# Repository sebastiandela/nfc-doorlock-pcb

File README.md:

# NFC-Controlled Electromagnetic Door Lock (Custom PCB)

The design files for a custom PCB created in Fusion 360 for an **NFC-controlled electromagnetic door lock**.

A **12V power supply** is used to power the eletromagnetic lock, NFC reader, and ATmega328P core. The schematic uses the Arduino Nano as the base and adds the additional functionality. 

## PCB Installation
This is an example of how the PCB can be used in a system.

## Board Layout

## 3D Model

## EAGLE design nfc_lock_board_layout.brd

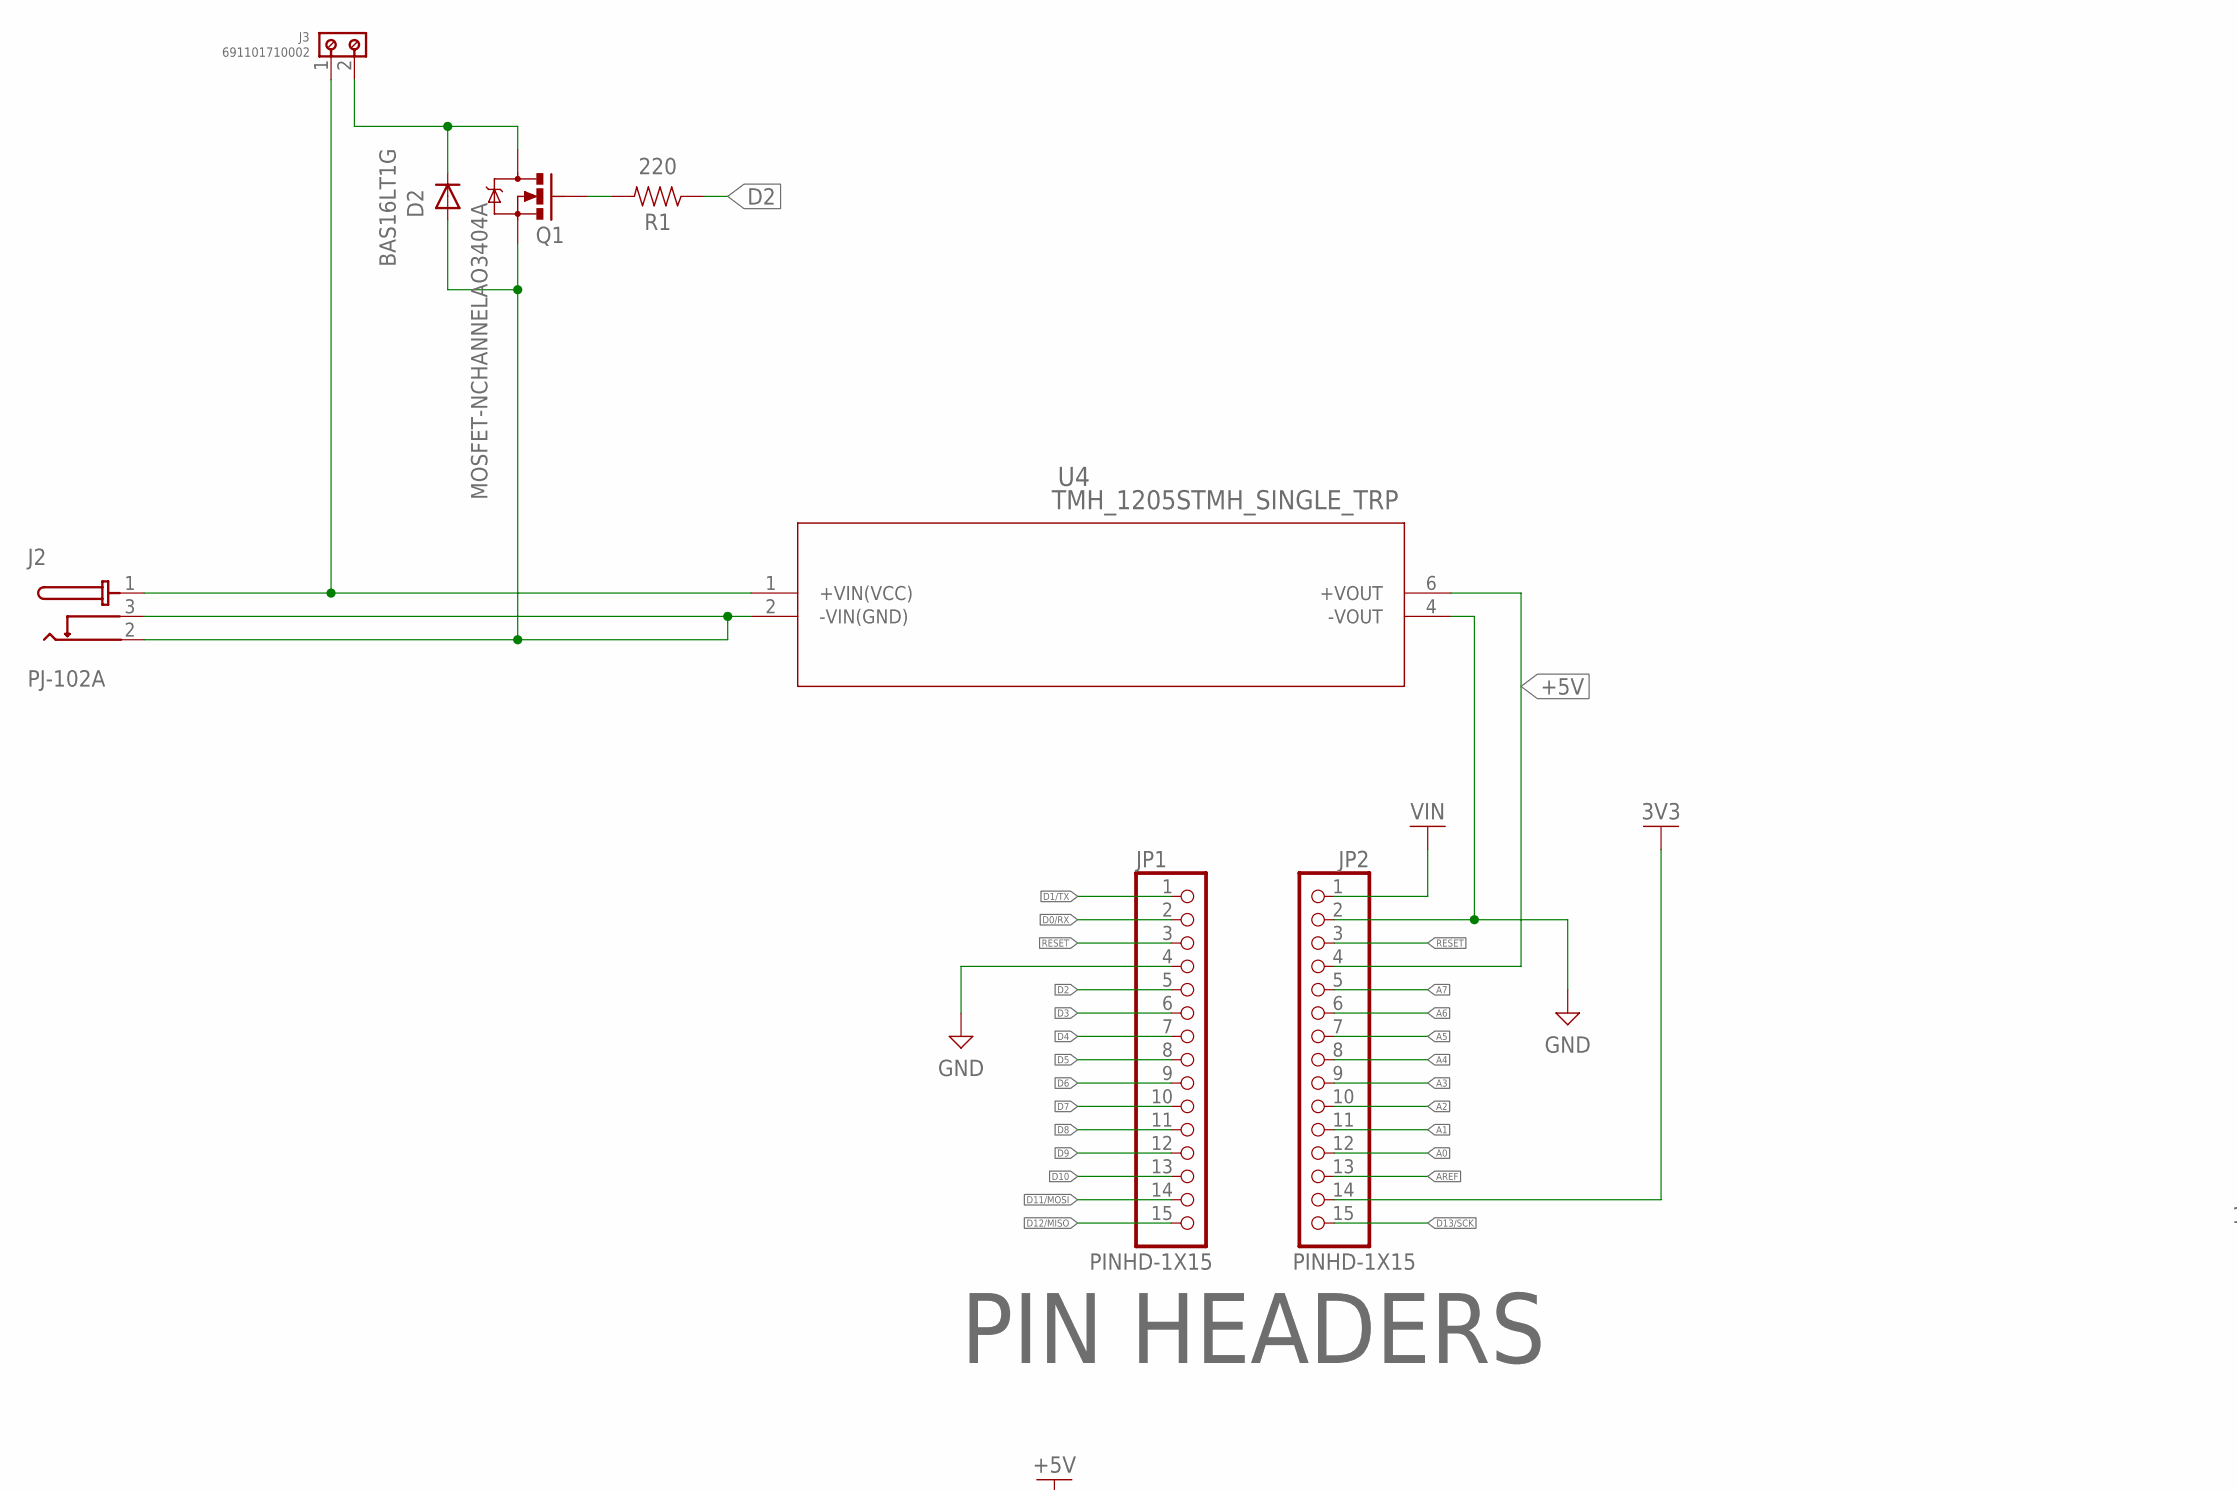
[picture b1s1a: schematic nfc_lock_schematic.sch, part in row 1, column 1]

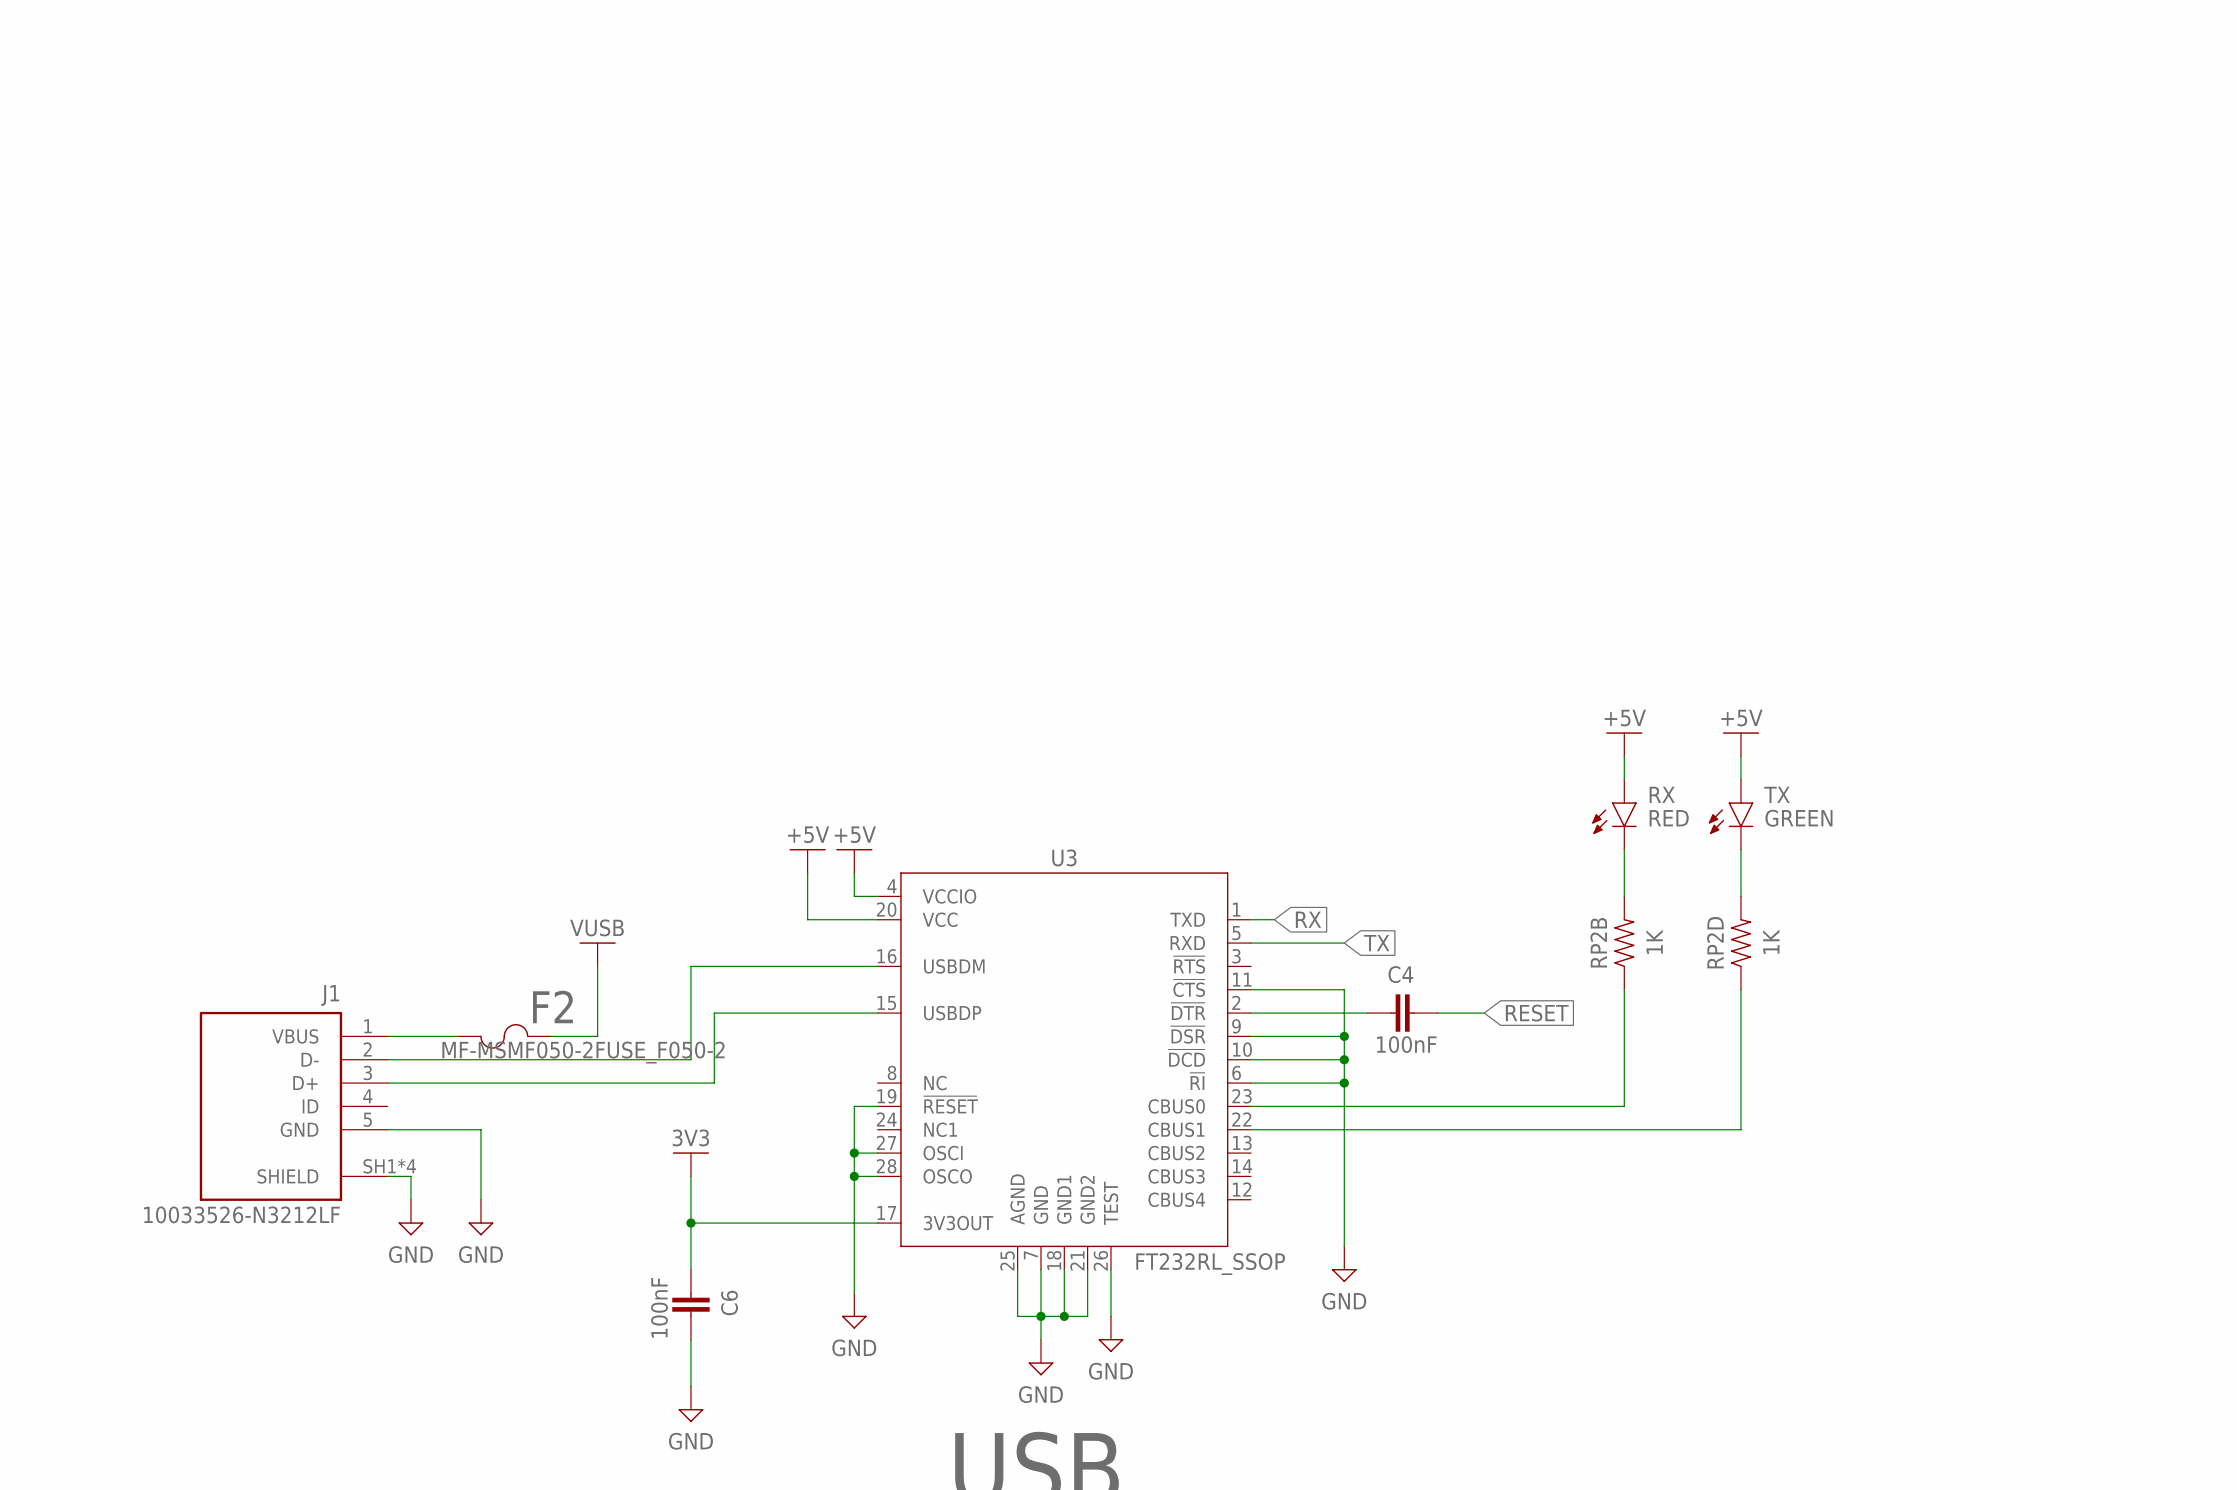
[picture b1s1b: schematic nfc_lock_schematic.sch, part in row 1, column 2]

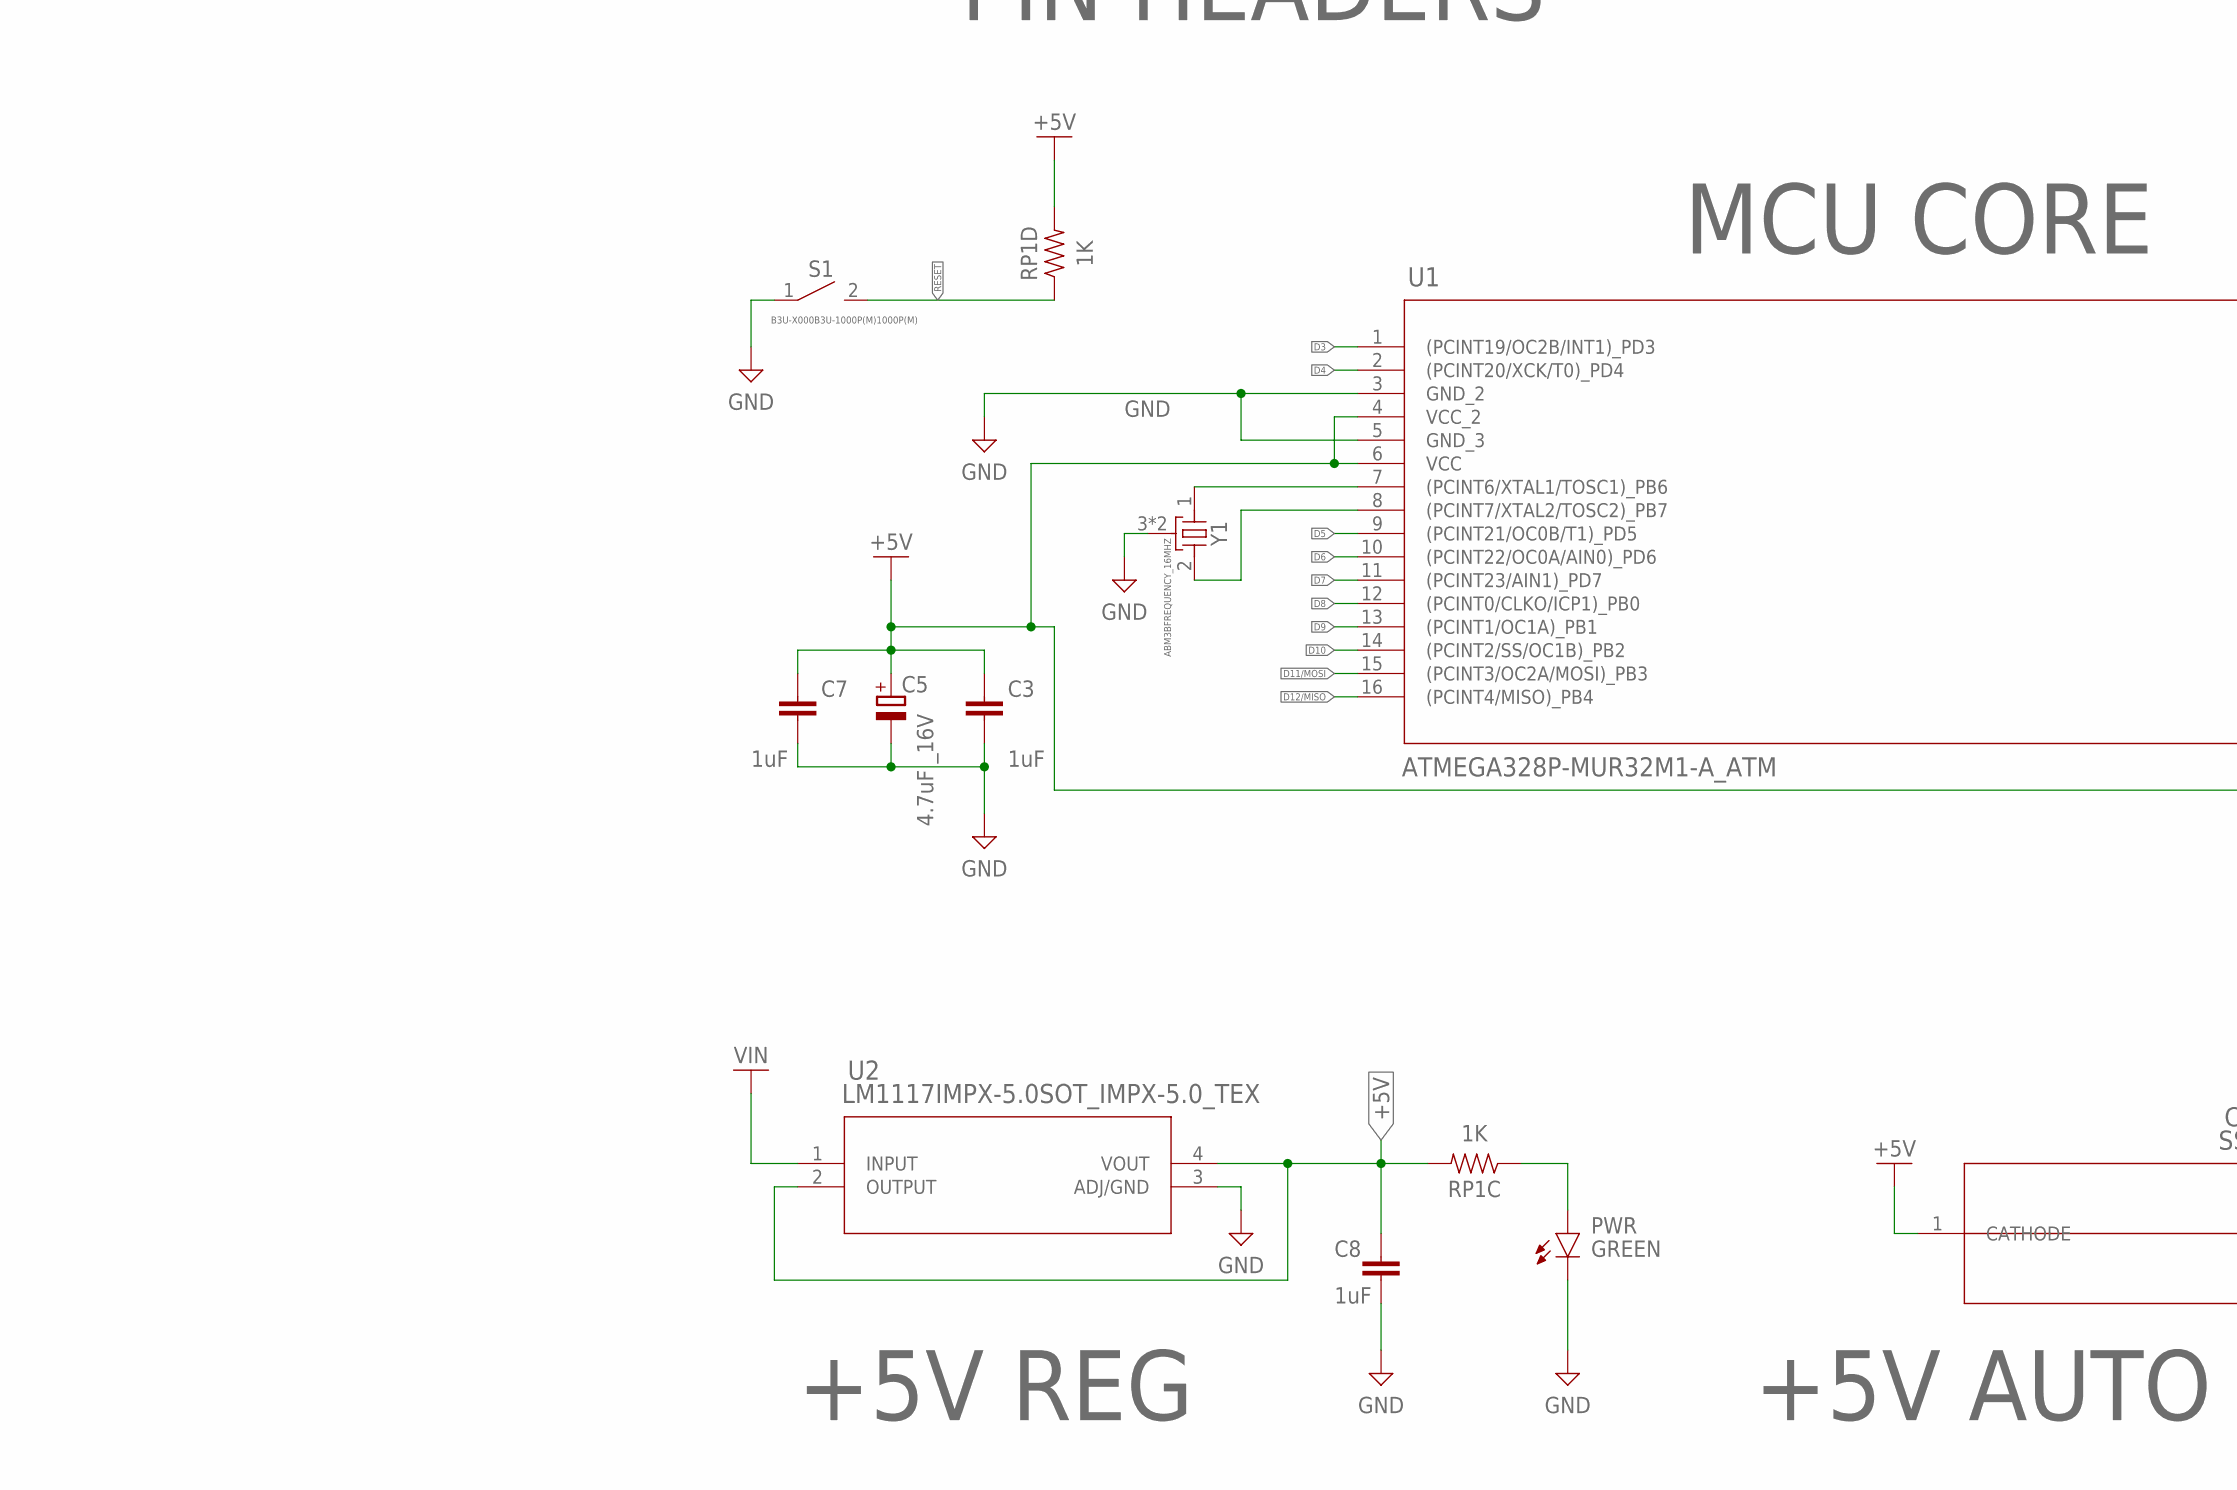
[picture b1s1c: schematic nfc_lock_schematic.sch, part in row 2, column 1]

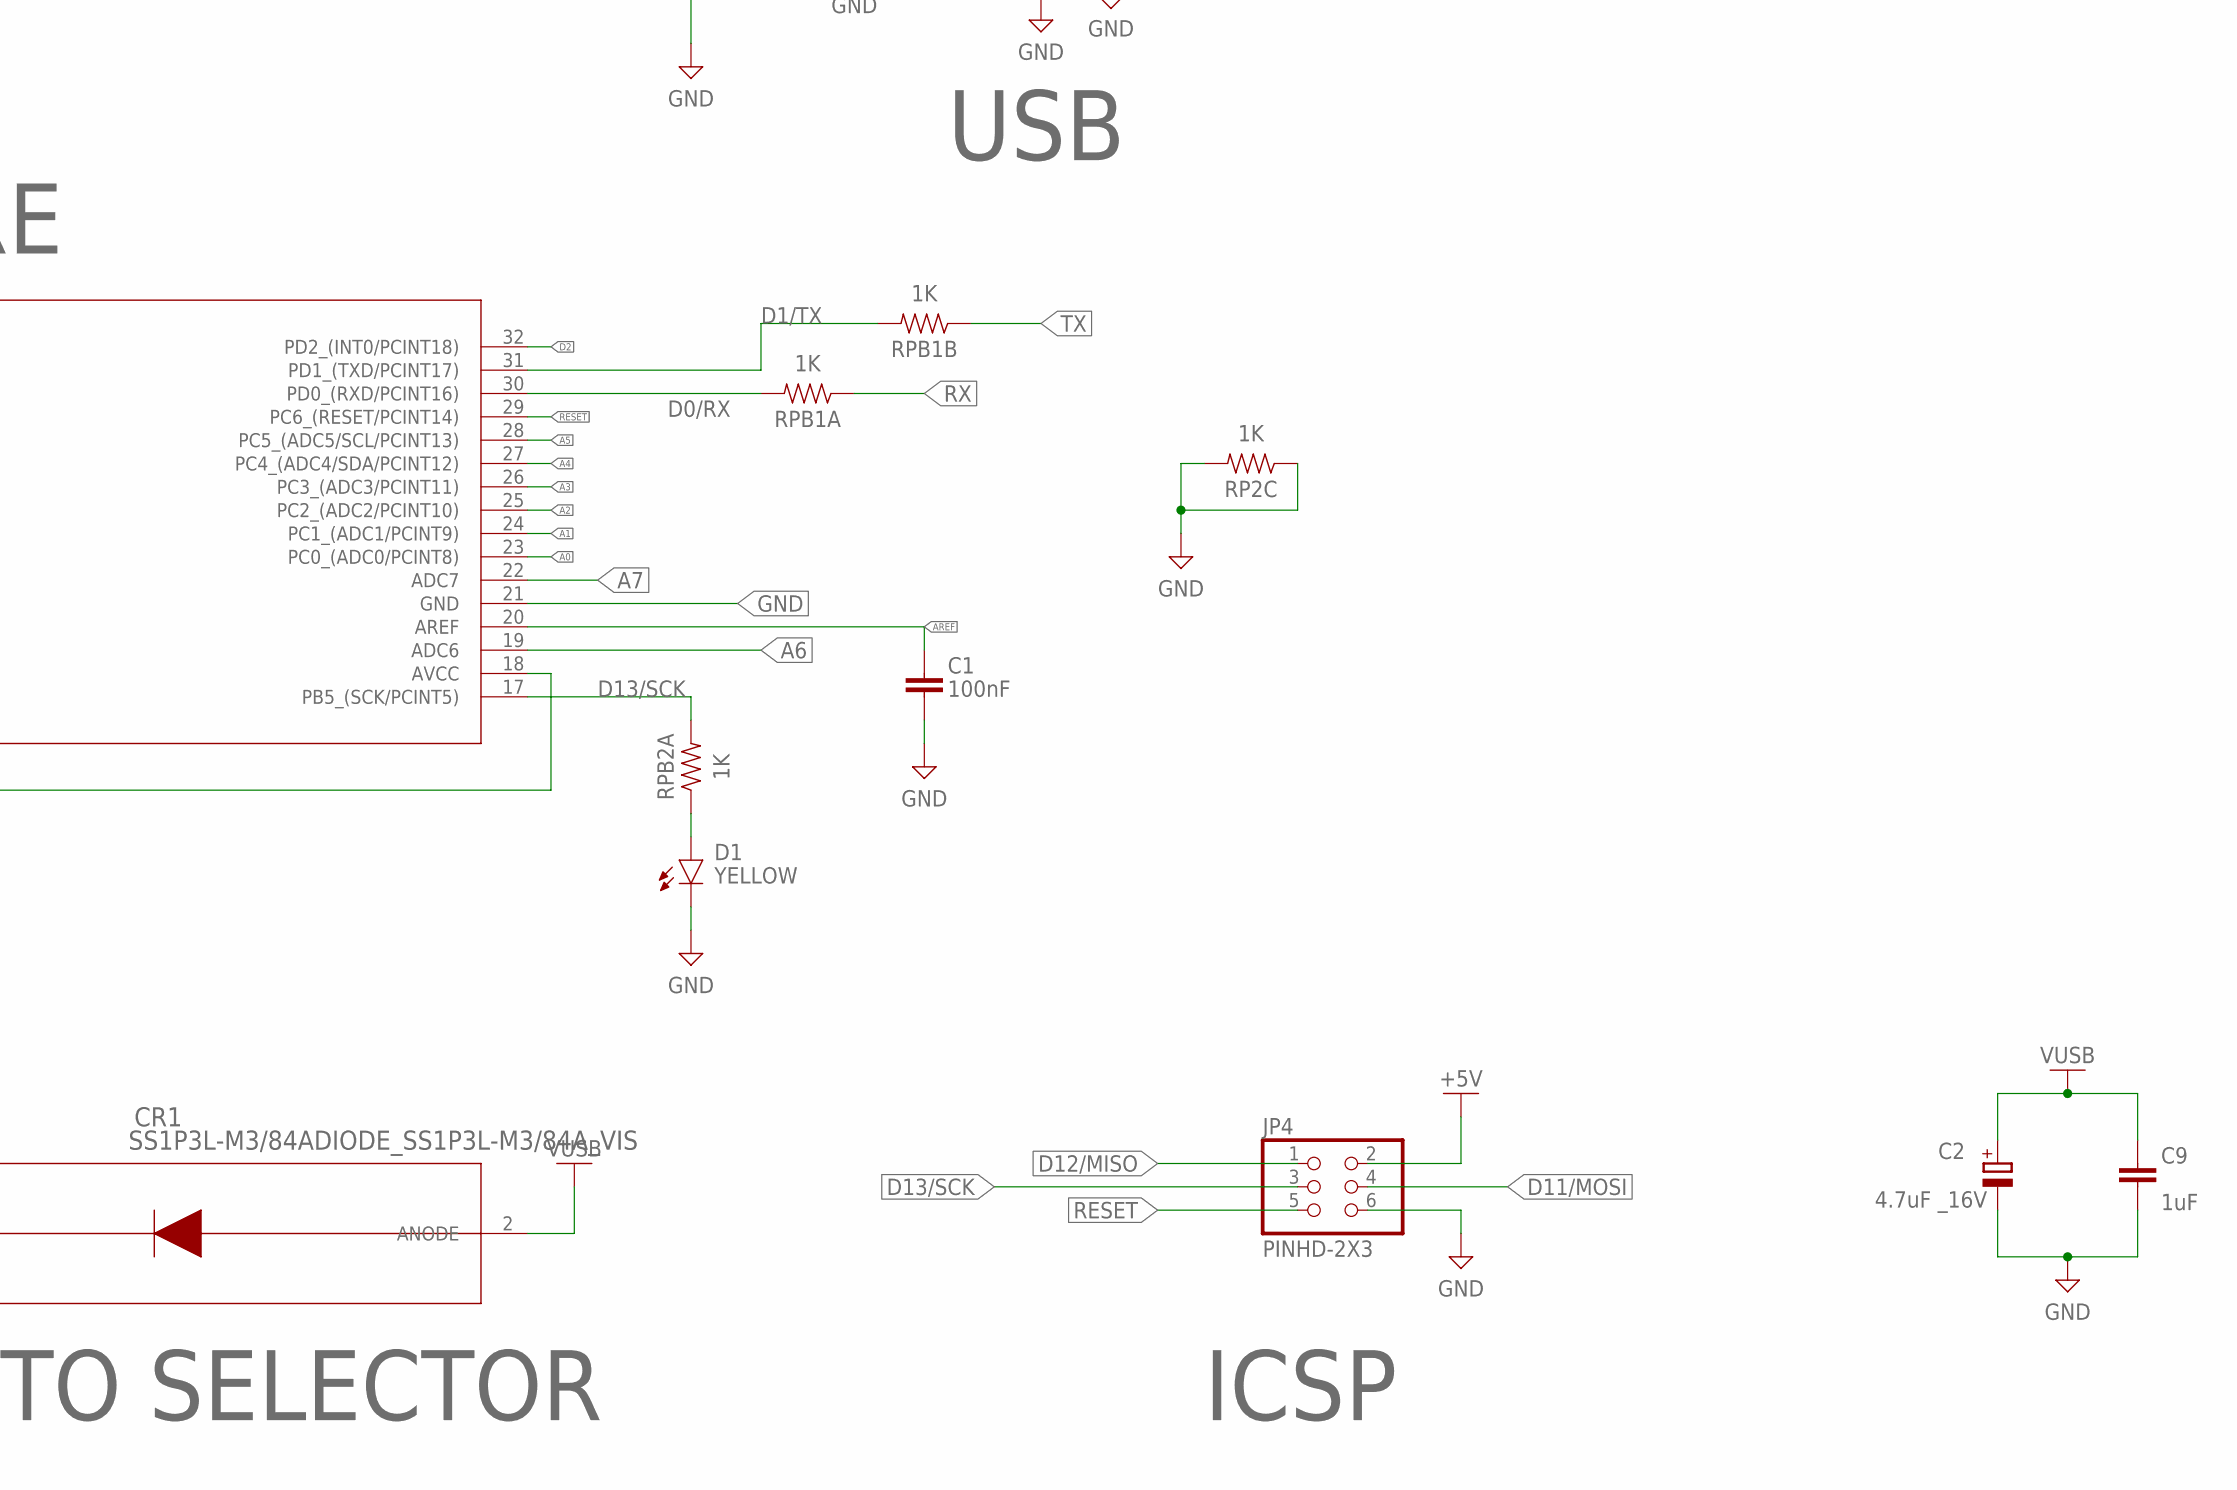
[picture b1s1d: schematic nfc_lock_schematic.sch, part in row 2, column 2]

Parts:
C1, C4, C6: 100nF; CAPC1005X60
C2, C5: 4.7uF _16V; CAPMP3216X180N
C3, C7, C8, C9: 1uF; CAPC1005X60
CR1: SS1P3L-M3/84ADIODE_SS1P3L-M3/84A_VIS; DIODE_SS1P3L-M3/84A_VIS
D1: YELLOW; LEDC1608X35N_FLAT-Y
D2: BAS16LT1G; SOT23
F2: MF-MSMF050-2FUSE_F050-2; FUSE_F050-2
J1: 10033526-N3212LF; AMPHENOL_10033526-N3212LF
J2: PJ-102A; CUI_PJ-102A
J3: 691101710002
JP1, JP2: PINHD-1X15; 1X15
JP4: PINHD-2X3; 2X03
PWR: GREEN; LEDC1608X35N_FLAT-G
Q1: MOSFET-NCHANNELAO3404A; SOT23-3
R1: 220; RESC1005X40
RP1C, RP1D, RP2B, RP2C, RP2D: 1K; RESC1005X40
RPB1A, RPB1B, RPB2A: 1K; RESC1005X40
RX: RED; LEDC1608X35N_FLAT-R
S1: B3U-X000B3U-1000P(M)1000P(M); B3U-1000P(M)
TX: GREEN; LEDC1608X35N_FLAT-G
U1: ATMEGA328P-MUR32M1-A_ATM; 32M1-A_ATM
U2: LM1117IMPX-5.0SOT_IMPX-5.0_TEX; SOT_IMPX-5.0_TEX
U3: FT232RL_SSOP; SSOP28
U4: TMH_1205STMH_SINGLE_TRP; TMH_SINGLE_TRP
Y1: ABM3BFREQUENCY_16MHZ; OSCSC500X320X110-4N

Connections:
3V3: C6.1, JP2.14, U3.17 (3V3OUT)
+5V: C3.1, C5.1 (+), C7.1, C8.1, CR1.1 (CATHODE), JP2.4, JP4.2, RP1C.2, RP1D.2, RX.A, TX.A, U1.4 (VCC_2), U1.6 (VCC), U1.18 (AVCC), U2.2 (OUTPUT), U2.4 (VOUT), U3.4 (VCCIO), U3.20 (VCC), U4.6 (+VOUT)
A0: JP2.12, U1.23 (PC0_(ADC0/PCINT8))
A1: JP2.11, U1.24 (PC1_(ADC1/PCINT9))
A2: JP2.10, U1.25 (PC2_(ADC2/PCINT10))
A3: JP2.9, U1.26 (PC3_(ADC3/PCINT11))
A4: JP2.8, U1.27 (PC4_(ADC4/SDA/PCINT12))
A5: JP2.7, U1.28 (PC5_(ADC5/SCL/PCINT13))
A6: JP2.6, U1.19 (ADC6)
A7: JP2.5, U1.22 (ADC7)
AREF: C1.1, JP2.13, U1.20 (AREF)
D0/RX: JP1.2, RPB1A.2, U1.30 (PD0_(RXD/PCINT16))
D1/TX: JP1.1, RPB1B.2, U1.31 (PD1_(TXD/PCINT17))
D2: JP1.5, Q1.1 (G), R1.1, R1.2, U1.32 (PD2_(INT0/PCINT18))
D3: JP1.6, U1.1 ((PCINT19/OC2B/INT1)_PD3)
D4: JP1.7, U1.2 ((PCINT20/XCK/T0)_PD4)
D5: JP1.8, U1.9 ((PCINT21/OC0B/T1)_PD5)
D6: JP1.9, U1.10 ((PCINT22/OC0A/AIN0)_PD6)
D7: JP1.10, U1.11 ((PCINT23/AIN1)_PD7)
D8: JP1.11, U1.12 ((PCINT0/CLKO/ICP1)_PB0)
D9: JP1.12, U1.13 ((PCINT1/OC1A)_PB1)
D10: JP1.13, U1.14 ((PCINT2/SS/OC1B)_PB2)
D11/MOSI: JP1.14, JP4.4, U1.15 ((PCINT3/OC2A/MOSI)_PB3)
D12/MISO: JP1.15, JP4.1, U1.16 ((PCINT4/MISO)_PB4)
D13/SCK: JP2.15, JP4.3, RPB2A.2, U1.17 (PB5_(SCK/PCINT5))
GND: C1.2, C2.2 (-), C3.2, C5.2 (-), C6.2, C7.2, C8.2, C9.2, D1.C, J1.5 (GND), J1.SH1 (SHIELD), J1.SH2 (SHIELD), J1.SH3 (SHIELD), J1.SH4 (SHIELD), JP1.4, JP2.2, JP4.6, PWR.C, RP2C.1, RP2C.2, S1.1, U1.3 (GND_2), U1.5 (GND_3), U1.21 (GND), U2.3 (ADJ/GND), U3.6 (!RI), U3.7 (GND), U3.9 (!DSR), U3.10 (!DCD), U3.11 (!CTS), U3.18 (GND1), U3.19 (!RESET), U3.21 (GND2), U3.25 (AGND), U3.26 (TEST), U3.27 (OSCI), U3.28 (OSCO), U4.4 (-VOUT), Y1.3 (GND), Y1.4 (GND)
unnamed: U1.8 ((PCINT7/XTAL2/TOSC2)_PB7), Y1.2
unnamed: U1.7 ((PCINT6/XTAL1/TOSC1)_PB6), Y1.1
unnamed: PWR.A, RP1C.1
unnamed: D1.A, RPB2A.1
unnamed: C4.1, U3.2 (!DTR)
unnamed: RP2B.1, U3.23 (CBUS0)
unnamed: RP2B.2, RX.C
unnamed: RP2D.1, U3.22 (CBUS1)
unnamed: RP2D.2, TX.C
unnamed: F2.2, J1.1 (VBUS)
unnamed: J1.2 (D-), U3.16 (USBDM)
unnamed: J1.3 (D+), U3.15 (USBDP)
unnamed: J2.1, J3.1, U4.1 (+VIN(VCC))
unnamed: D2.3 (K), J3.2, Q1.3 (D)
unnamed: D2.1 (A), J2.2, J2.3, Q1.2 (S), U4.2 (-VIN(GND))
RESET: C4.2, JP1.3, JP2.3, JP4.5, RP1D.1, S1.2, U1.29 (PC6_(RESET/PCINT14))
RX: RPB1A.1, U3.1 (TXD)
TX: RPB1B.1, U3.5 (RXD)
VIN: JP2.1, U2.1 (INPUT)
VUSB: C2.1 (+), C9.1, CR1.2 (ANODE), F2.1

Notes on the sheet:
MCU CORE
+5V REG
+5V AUTO SELECTOR
ICSP
PIN HEADERS
USB

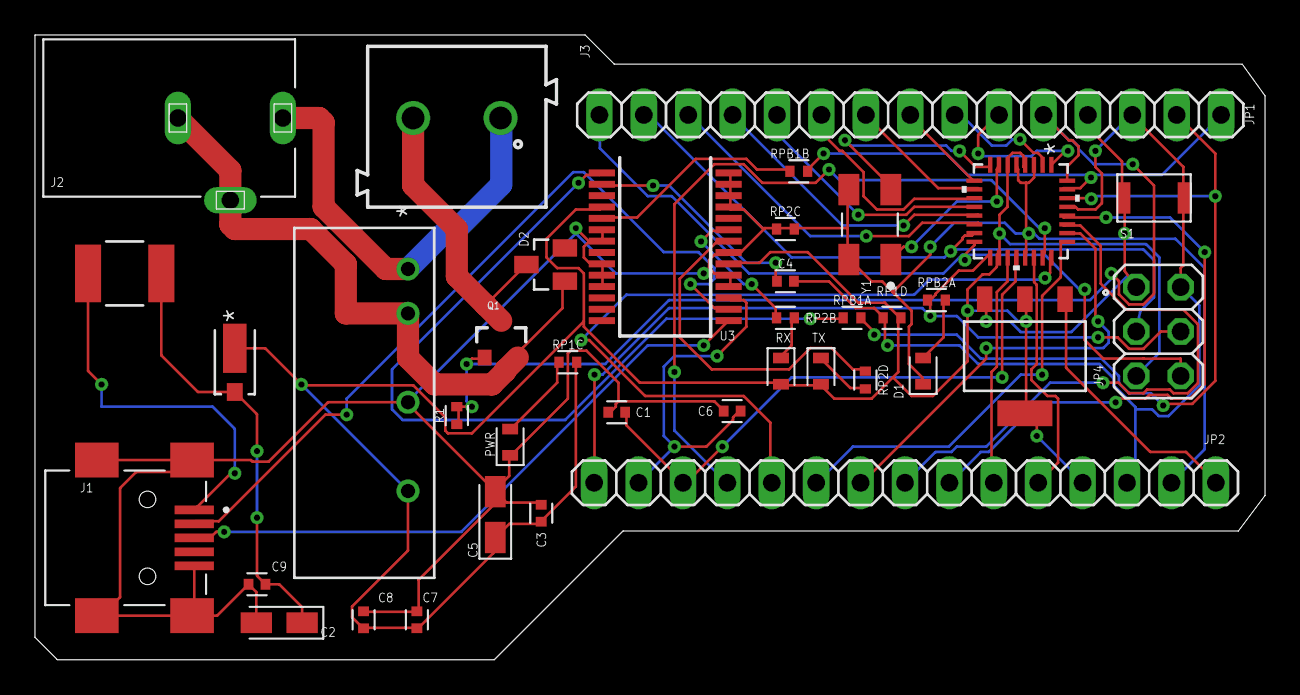
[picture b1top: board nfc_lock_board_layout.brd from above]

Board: 2 copper layers, 70.4 x 35.7 mm, 38 parts (0 on the bottom side), 46 nets.

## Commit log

2025-06-08 Upload pcb files
2025-06-08 Add pcb implementation diagram

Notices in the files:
parts and their libraries:
691137710002: Copyright: Würth Elektronik
COPYRIGHT: Copyright (C) 2025 Ultra Librarian. All rights reserved.
